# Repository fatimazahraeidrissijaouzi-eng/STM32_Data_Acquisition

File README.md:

# STM32 Data Acquisition Board & Real-Time Embedded System

**STM32F103C8Tx · KiCad · STM32CubeIDE · Embedded C · FreeRTOS**

A hardware/software engineering project combining a custom two-layer STM32 data-acquisition PCB with embedded firmware for ADC sampling and UART communication.

## Project overview

- **Hardware:** STM32F103C8Tx schematic and 2-layer PCB designed in KiCad, with reset circuitry, decoupling capacitors, and headers for SWD, ADC, UART, I2C and SPI.
- **PCB fabrication outputs:** front/back copper, solder masks, silkscreens, board outline, and plated/non-plated drill files generated from the routed board.
- **Firmware:** STM32CubeIDE project using STM32 HAL, ADC, USART, I2C, SPI, timer configuration and FreeRTOS tasks for acquisition and communication.
- **Verification:** KiCad ERC/DRC checks performed; firmware compiled successfully in STM32CubeIDE; ADC arithmetic test cases exercised separately.

## Repository structure (target layout)

```text
hardware/
  kicad/                KiCad schematic, project and routed PCB
  gerbers/              Fabrication outputs
firmware/
  Core/                 Application sources and headers
  Drivers/              STM32 HAL and CMSIS dependencies
  Middlewares/          FreeRTOS middleware
  tests/                Firmware-related tests
  STM32_Data_Acquisition_FW.ioc
scripts/                KiCad automation scripts
docs/                   Verification reports and project images
```

> **Publication status:** Files are being added progressively. The directory tree above describes the intended complete release; not all paths are necessarily present yet.

## Verification status and limitations

The PCB design was routed and fabrication outputs generated. Earlier checks reported no DRC violations or unrouted connections, with certain check categories ignored; schematic-to-PCB parity was not established by those results. The firmware was reported to compile without errors or warnings. ADC calculations were tested separately, but these are **not** evidence of complete embedded runtime verification.

**No physical STM32 board was manufactured or tested.** Hardware behavior, UART traffic and FreeRTOS scheduling have not been validated on a real device. Component placement, especially proximity of decoupling capacitors to MCU power pins, should be reviewed before fabrication.

## Tools

KiCad 10, STM32CubeIDE, Embedded C, STM32 HAL, FreeRTOS, Python.

## License

See the repository license for original project material. Third-party STM32 HAL, CMSIS and FreeRTOS files retain their own applicable notices and licenses.

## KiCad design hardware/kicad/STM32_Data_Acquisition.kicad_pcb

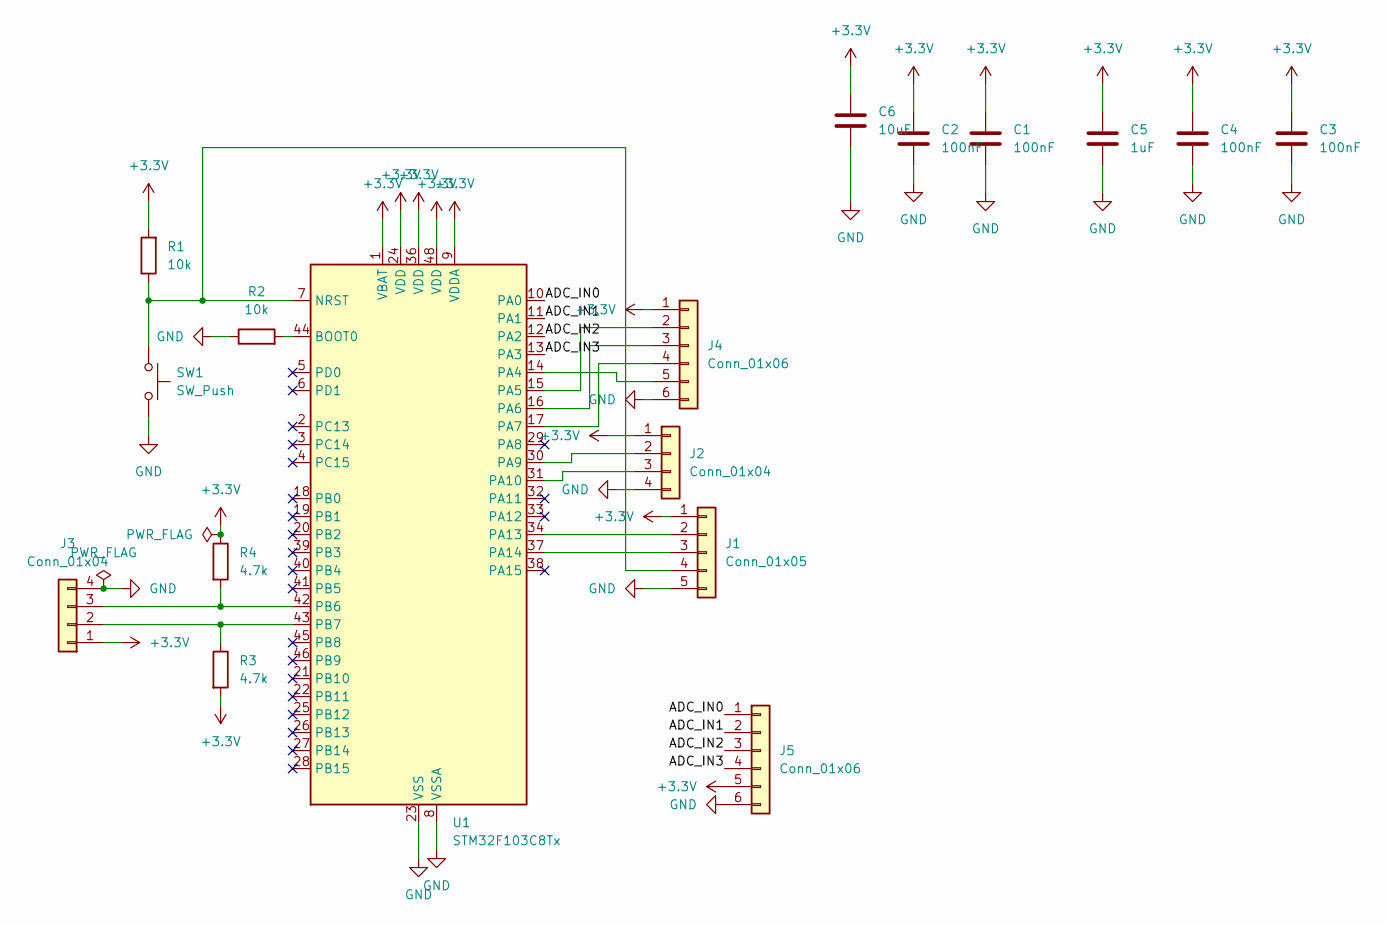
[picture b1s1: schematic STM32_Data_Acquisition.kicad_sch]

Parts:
C1, C2, C3, C4: 100nF; C_0805_2012Metric
C5: 1uF; C_0805_2012Metric
C6: 10uF; C_0805_2012Metric
J1: Conn_01x05; PinHeader_1x05_P2.54mm_Vertical
J2, J3: Conn_01x04; PinHeader_1x04_P2.54mm_Vertical
J4, J5: Conn_01x06; PinHeader_1x06_P2.54mm_Vertical
R1, R2: 10k; R_0805_2012Metric
R3, R4: 4.7k; R_0805_2012Metric
SW1: SW_Push; SW_SPST_TL3305A
U1: STM32F103C8Tx; LQFP-48_7x7mm_P0.5mm

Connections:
+3.3V: C1.1, C2.1, C3.1, C4.1, C5.1, C6.1, J1.1, J2.1, J3.1, J4.1, J5.5, R1.2, R3.2, R4.1, U1.1 (VBAT), U1.9 (VDDA), U1.24 (VDD), U1.36 (VDD), U1.48 (VDD)
/ADC_IN0: J5.1, U1.10 (PA0)
/ADC_IN1: J5.2, U1.11 (PA1)
/ADC_IN2: J5.3, U1.12 (PA2)
/ADC_IN3: J5.4, U1.13 (PA3)
GND: C1.2, C2.2, C3.2, C4.2, C5.2, C6.2, J1.5, J2.4, J3.4, J4.6, J5.6, R2.1, SW1.2, U1.8 (VSSA), U1.23 (VSS), U1.35 (VSS), U1.47 (VSS)
unnamed: J1.2, U1.34 (PA13)
unnamed: J1.3, U1.37 (PA14)
unnamed: J1.4, R1.1, SW1.1, U1.7 (NRST)
unnamed: J2.2, U1.30 (PA9)
unnamed: J2.3, U1.31 (PA10)
unnamed: J3.2, R3.1, U1.43 (PB7)
unnamed: J3.3, R4.2, U1.42 (PB6)
unnamed: J4.2, U1.15 (PA5)
unnamed: J4.3, U1.16 (PA6)
unnamed: J4.4, U1.17 (PA7)
unnamed: J4.5, U1.14 (PA4)
unnamed: R2.2, U1.44 (BOOT0)

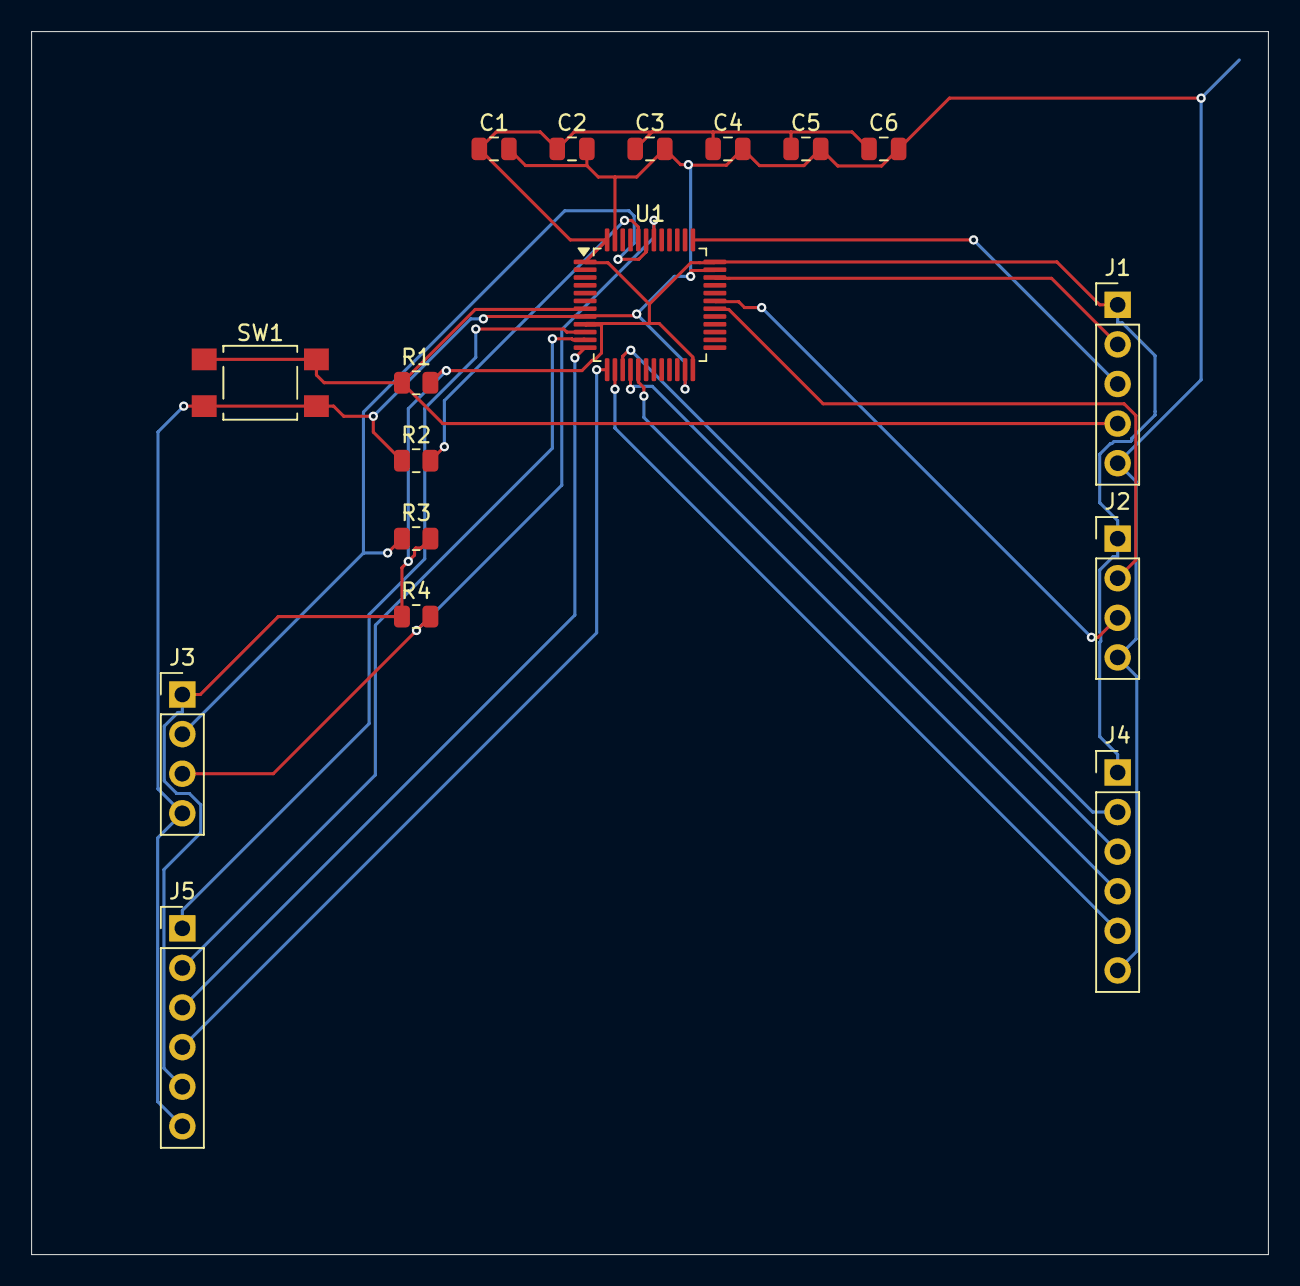
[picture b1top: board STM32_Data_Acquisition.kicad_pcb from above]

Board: 2 copper layers, 79.3 x 78.5 mm, 17 parts (0 on the bottom side), 18 nets.

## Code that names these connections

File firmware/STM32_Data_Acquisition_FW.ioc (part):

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Mcu.Name=STM32F103C(8-B)Tx
Mcu.Package=LQFP48
Mcu.UserName=STM32F103C8Tx
PA0-WKUP.Signal=ADCx_IN0
PA10.Mode=Asynchronous
PA10.Signal=USART1_RX
PA13.Mode=Serial_Wire
PA13.Signal=SYS_JTMS-SWDIO
PA14.Mode=Serial_Wire
PA14.Signal=SYS_JTCK-SWCLK
PA4.GPIOParameters=PinState
PA4.PinState=GPIO_PIN_SET
PA4.Signal=GPIO_Output
PA5.Mode=Full_Duplex_Master
PA5.Signal=SPI1_SCK
PA6.Mode=Full_Duplex_Master
PA6.Signal=SPI1_MISO
PA7.Mode=Full_Duplex_Master
PA7.Signal=SPI1_MOSI
PA9.Mode=Asynchronous
PA9.Signal=USART1_TX
PB6.Mode=I2C
PB6.Signal=I2C1_SCL
PB7.Mode=I2C
PB7.Signal=I2C1_SDA
board=custom
